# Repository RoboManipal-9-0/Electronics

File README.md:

# Electronics

All the CAD files of the PCBs that electronics team designs goes here

## Note for Users

Only master branch has completed CAD, so make sure to use only them.

## Note for Collaboraters

Before doing anything here learn how to use git version control(different from github), i'll attach the links below
- [Introduction to git- core concepts](https://youtu.be/uR6G2v_WsRA)
- [Introduction to git- Branching and Merging](https://youtu.be/FyAAIHHClqI)
- [Introduction to git- Remotes](https://youtu.be/Gg4bLk8cGNo)

Create a branch with the name of your board that you are working on and start working on that. If two people are woking on same board, add your name at the end seperated with a "-". Don't push any incomplete work to master, keep it clean.

Once you are done designing everthing, add the gerber files in a seperate zip file, merge your branch to master and delete the branch.

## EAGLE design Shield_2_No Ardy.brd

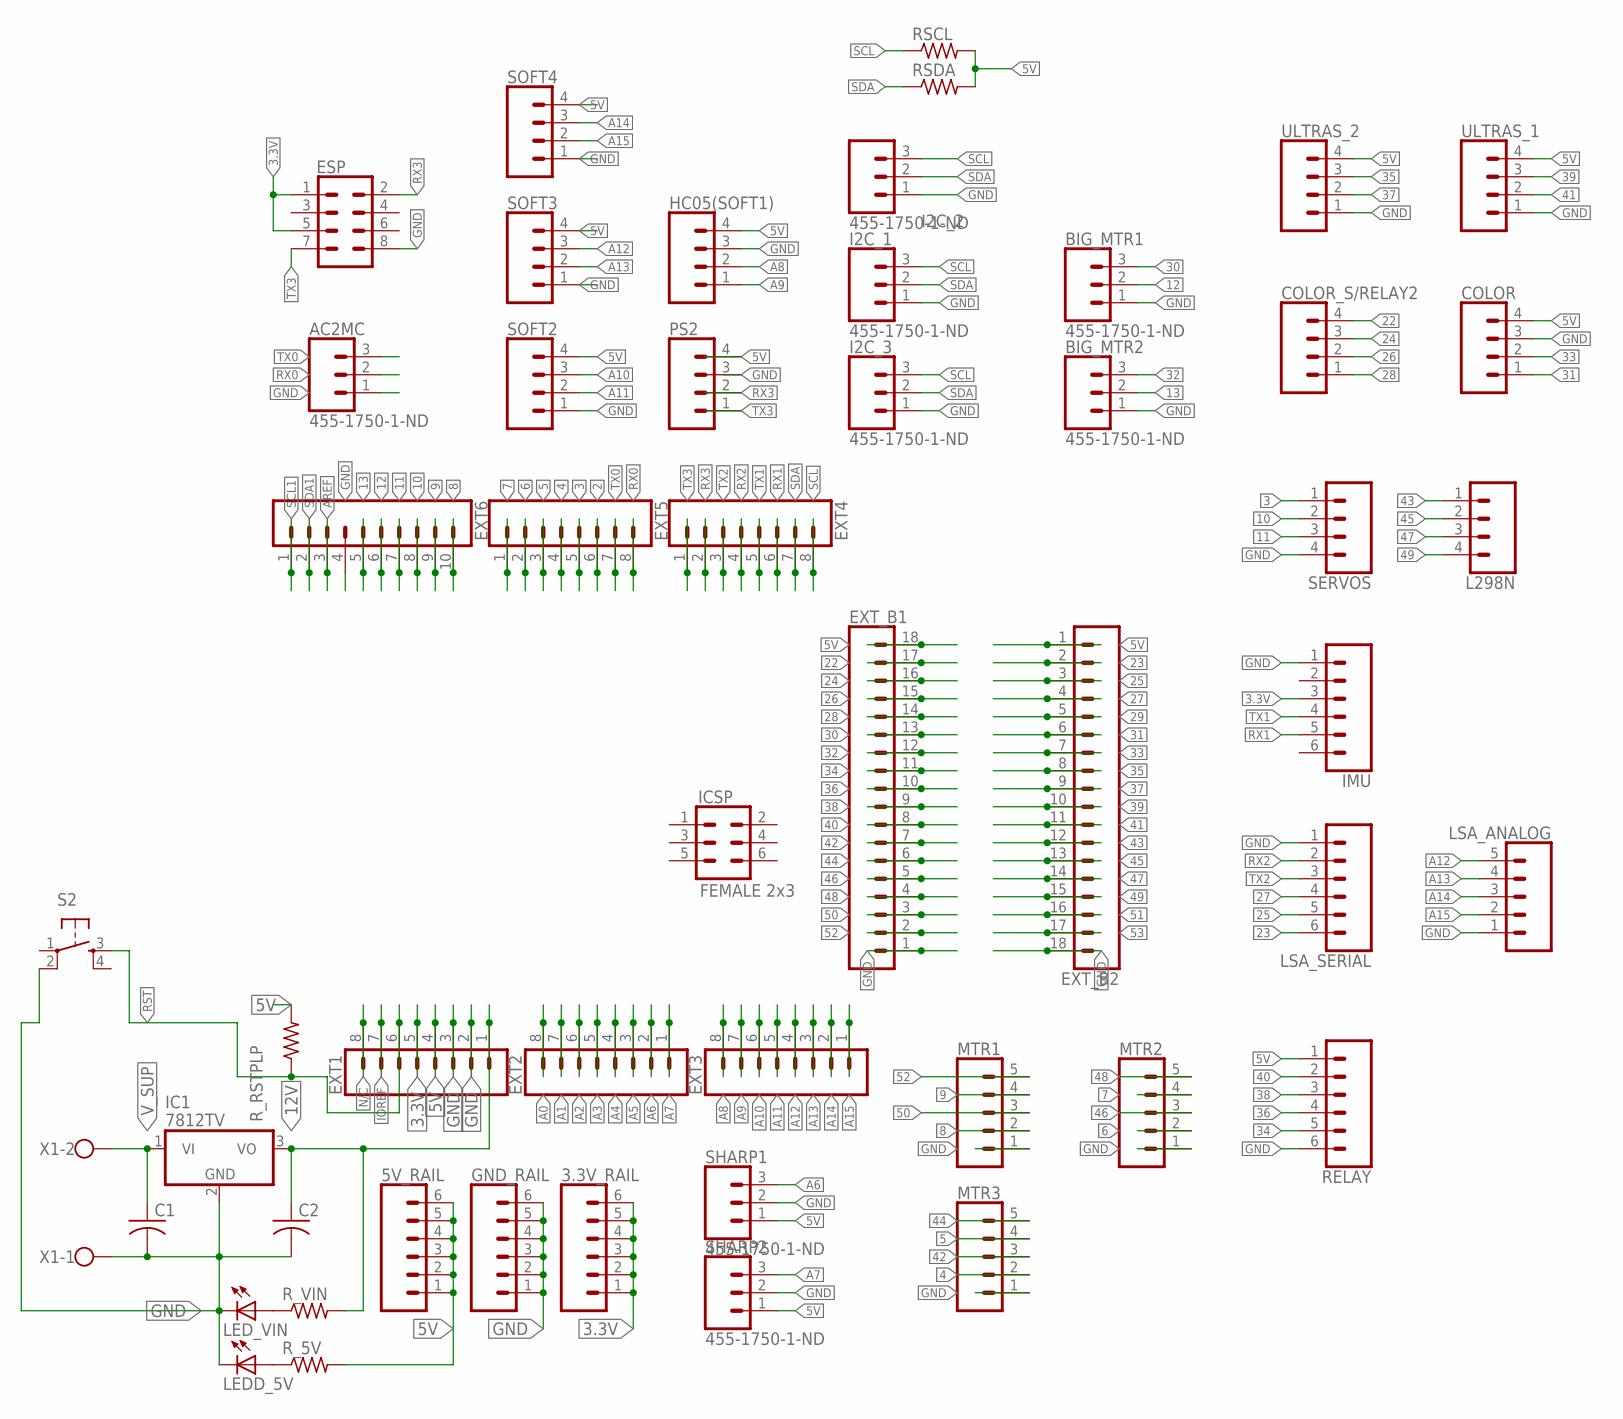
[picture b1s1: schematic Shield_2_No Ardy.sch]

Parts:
3.3V_RAIL, 5V_RAIL: CONN_06SILK_FEMALE_PTH; 1X06
AC2MC: 455-1750-1-ND; 1X03
BIG_MTR1, BIG_MTR2: 455-1750-1-ND; 1X03
C1, C2: C-US025-024X044; C025-024X044
COLOR: CONN_04; 1X04
COLOR_S/RELAY2: CONN_04; 1X04
ESP: CONN_04X2; 2X4
EXT1, EXT2, EXT3, EXT4, EXT5: CONN_08"; 1X08
EXT6: CONN_10"; 1X10
EXT_B1, EXT_B2: CONN_18; 1X18_NO_SILK
GND_RAIL: CONN_06SILK_FEMALE_PTH; 1X06
HC05(SOFT1): CONN_04; 1X04
I2C_1, I2C_2, I2C_3: 455-1750-1-ND; 1X03
IC1: 7812TV; TO220V
ICSP: FEMALE 2x3; 2X3
IMU: CONN_06SILK_FEMALE_PTH; 1X06
L298N: CONN_04; 1X04
LEDD_5V: LED5MM
LED_VIN: LED5MM
LSA_ANALOG: CONN_05; 1X05
LSA_SERIAL: CONN_06SILK_FEMALE_PTH; 1X06
MTR1, MTR2, MTR3: CONN_05; 1X05
PS2: CONN_04; 1X04
RELAY: CONN_06SILK_FEMALE_PTH; 1X06
RSCL: R-US_0204/7; 0204/7
RSDA: R-US_0204/7; 0204/7
R_5V: R-US_0204/7; 0204/7
R_RSTPLP: R-US_0204/7; 0204/7
R_VIN: R-US_0204/7; 0204/7
S2: TAC_SWITCHPTH; TACTILE-PTH
SERVOS: CONN_04; 1X04
SHARP1, SHARP2: 455-1750-1-ND; 1X03
SOFT2, SOFT3, SOFT4: CONN_04; 1X04
ULTRAS_1, ULTRAS_2: CONN_04; 1X04
X1: W237-102

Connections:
2: EXT5.6
3: EXT5.5, SERVOS.1
3.3V: 3.3V_RAIL.1, 3.3V_RAIL.2, 3.3V_RAIL.3, 3.3V_RAIL.4, 3.3V_RAIL.5, 3.3V_RAIL.6, ESP.1, ESP.5, EXT1.5, IMU.3
4: EXT5.4, MTR3.2
5: EXT5.3, MTR3.4
5V: 5V_RAIL.1, 5V_RAIL.2, 5V_RAIL.3, 5V_RAIL.4, 5V_RAIL.5, 5V_RAIL.6, COLOR.4, EXT1.4, EXT_B1.18, EXT_B2.1, HC05(SOFT1).4, PS2.4, RELAY.1, RSCL.2, RSDA.2, R_5V.2, R_RSTPLP.2, SHARP1.1, SHARP2.1, SOFT2.4, SOFT3.4, SOFT4.4, ULTRAS_1.4, ULTRAS_2.4
6: EXT5.2, MTR2.2
7: EXT5.1, MTR2.4
8: EXT6.10, MTR1.2
9: EXT6.9, MTR1.4
10: EXT6.8, SERVOS.2
11: EXT6.7, SERVOS.3
12: BIG_MTR1.2, EXT6.6
12V: C2.1, EXT1.1, IC1.3 (VO), R_VIN.2
13: BIG_MTR2.2, EXT6.5
22: COLOR_S/RELAY2.4, EXT_B1.17
23: EXT_B2.2, LSA_SERIAL.6
24: COLOR_S/RELAY2.3, EXT_B1.16
25: EXT_B2.3, LSA_SERIAL.5
26: COLOR_S/RELAY2.2, EXT_B1.15
27: EXT_B2.4, LSA_SERIAL.4
28: COLOR_S/RELAY2.1, EXT_B1.14
29: EXT_B2.5
30: BIG_MTR1.3, EXT_B1.13
31: COLOR.1, EXT_B2.6
32: BIG_MTR2.3, EXT_B1.12
33: COLOR.2, EXT_B2.7
34: EXT_B1.11, RELAY.5
35: EXT_B2.8, ULTRAS_2.3
36: EXT_B1.10, RELAY.4
37: EXT_B2.9, ULTRAS_2.2
38: EXT_B1.9, RELAY.3
39: EXT_B2.10, ULTRAS_1.3
40: EXT_B1.8, RELAY.2
41: EXT_B2.11, ULTRAS_1.2
42: EXT_B1.7, MTR3.3
43: EXT_B2.12, L298N.1
44: EXT_B1.6, MTR3.5
45: EXT_B2.13, L298N.2
46: EXT_B1.5, MTR2.3
47: EXT_B2.14, L298N.3
48: EXT_B1.4, MTR2.5
49: EXT_B2.15, L298N.4
50: EXT_B1.3, MTR1.3
51: EXT_B2.16
52: EXT_B1.2, MTR1.5
53: EXT_B2.17
A0: EXT2.8
A1: EXT2.7
A2: EXT2.6
A3: EXT2.5
A4: EXT2.4
A5: EXT2.3
A6: EXT2.2, SHARP1.3
A7: EXT2.1, SHARP2.3
A8: EXT3.8, HC05(SOFT1).2
A9: EXT3.7, HC05(SOFT1).1
A10: EXT3.6, SOFT2.3
A11: EXT3.5, SOFT2.2
A12: EXT3.4, LSA_ANALOG.5, SOFT3.3
A13: EXT3.3, LSA_ANALOG.4, SOFT3.2
A14: EXT3.2, LSA_ANALOG.3, SOFT4.3
A15: EXT3.1, LSA_ANALOG.2, SOFT4.2
AREF: EXT6.3
GND: AC2MC.1, BIG_MTR1.1, BIG_MTR2.1, C1.2, C2.2, COLOR.3, ESP.8, EXT1.2, EXT1.3, EXT6.4, EXT_B1.1, EXT_B2.18, GND_RAIL.1, GND_RAIL.2, GND_RAIL.3, GND_RAIL.4, GND_RAIL.5, GND_RAIL.6, HC05(SOFT1).3, I2C_1.1, I2C_2.1, I2C_3.1, IC1.2 (GND), IMU.1, LEDD_5V.K (C), LED_VIN.K (C), LSA_ANALOG.1, LSA_SERIAL.1, MTR1.1, MTR2.1, MTR3.1, PS2.3, RELAY.6, S2.2, SERVOS.4, SHARP1.2, SHARP2.2, SOFT2.1, SOFT3.1, SOFT4.1, ULTRAS_1.1, ULTRAS_2.1, X1.1
IOREF: EXT1.7
unnamed: LED_VIN.A, R_VIN.1
unnamed: LEDD_5V.A, R_5V.1
N/C: EXT1.8
RST: EXT1.6, R_RSTPLP.1, S2.3
RX0: AC2MC.2, EXT5.8
RX1: EXT4.6, IMU.5
RX2: EXT4.4, LSA_SERIAL.2
RX3: ESP.2, EXT4.2, PS2.2
SCL: EXT4.8, I2C_1.3, I2C_2.3, I2C_3.3, RSCL.1
SCL1: EXT6.1
SDA: EXT4.7, I2C_1.2, I2C_2.2, I2C_3.2, RSDA.1
SDA1: EXT6.2
TX0: AC2MC.3, EXT5.7
TX1: EXT4.5, IMU.4
TX2: EXT4.3, LSA_SERIAL.3
TX3: ESP.7, EXT4.1, PS2.1
V_SUP: C1.1, IC1.1 (VI), X1.2

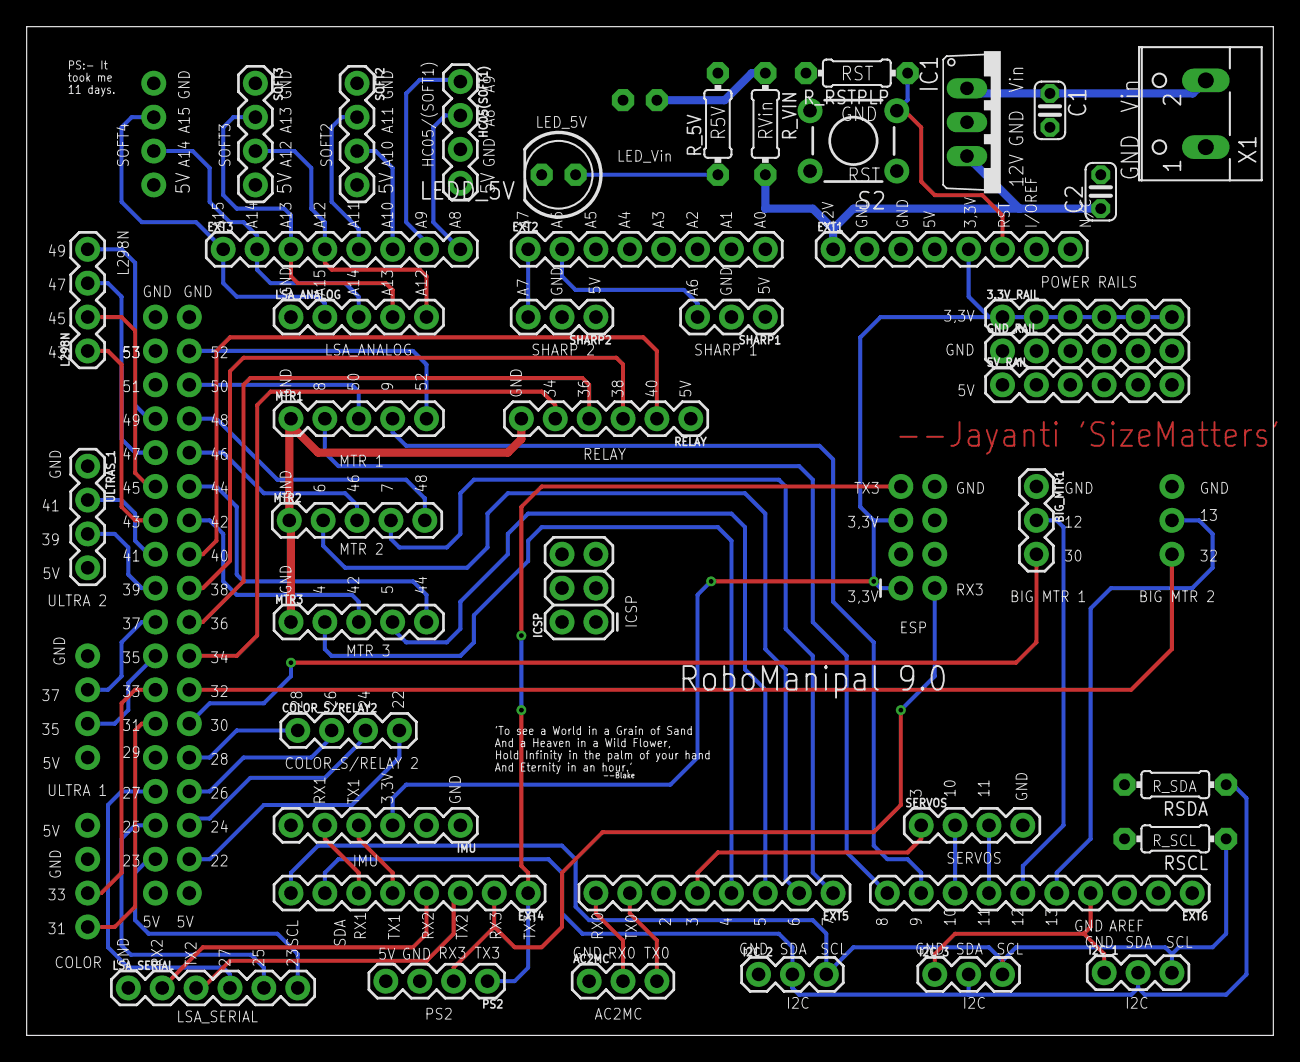
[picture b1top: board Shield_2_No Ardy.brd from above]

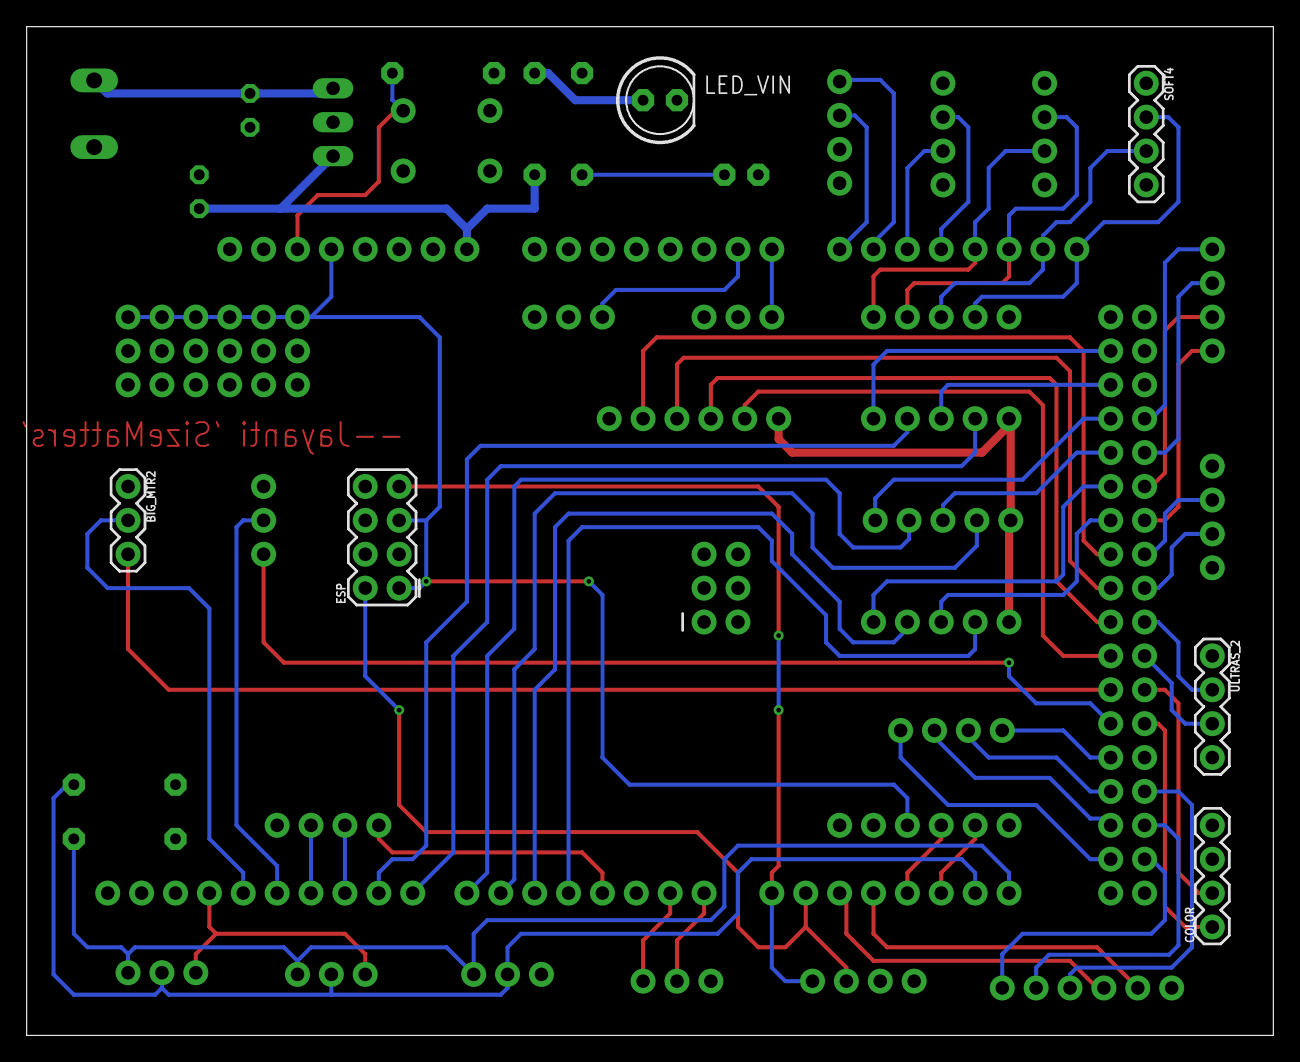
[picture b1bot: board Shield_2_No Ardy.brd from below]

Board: 2 copper layers, 93.5 x 75.6 mm, 51 parts (7 on the bottom side), 68 nets.

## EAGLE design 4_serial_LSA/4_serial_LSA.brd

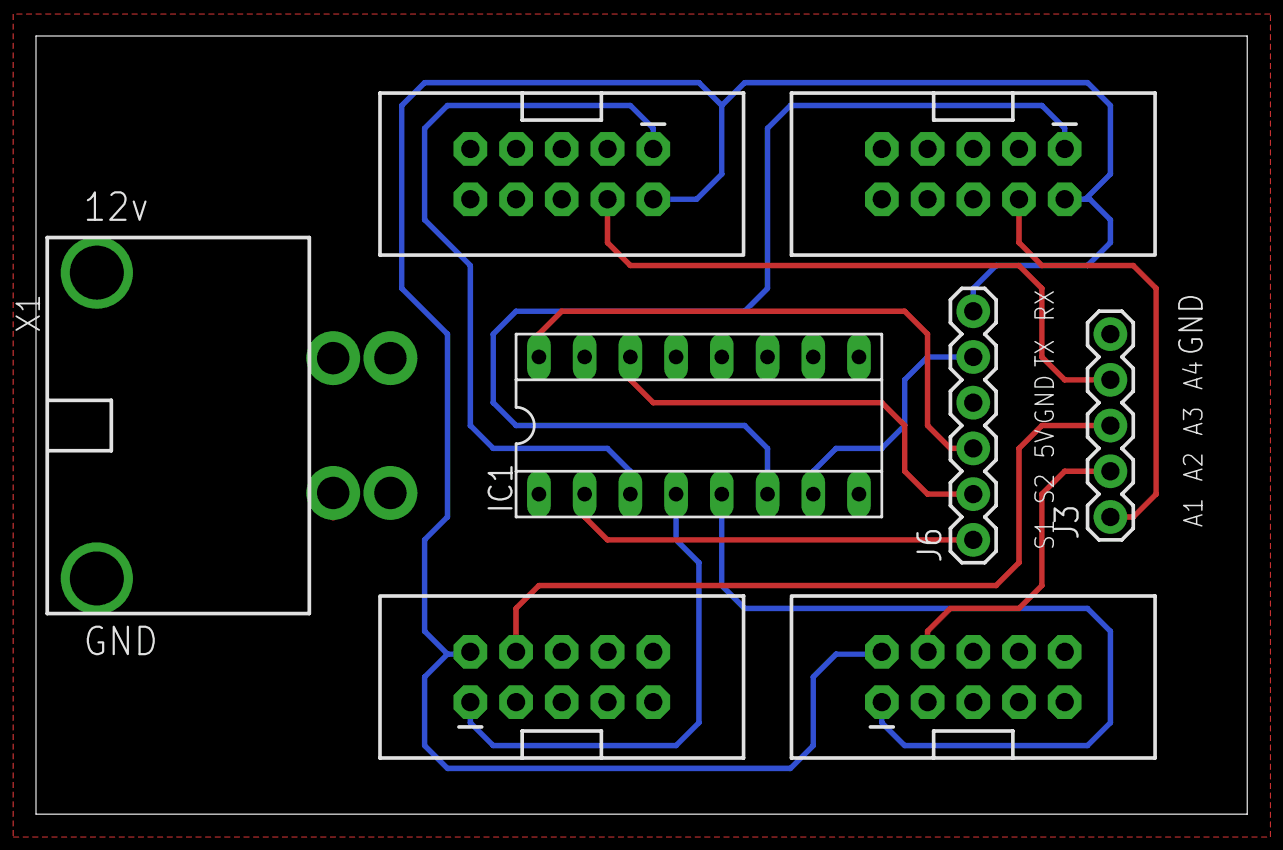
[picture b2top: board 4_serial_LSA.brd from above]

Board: 2 copper layers, 67.3 x 43.2 mm, 8 parts (0 on the bottom side), 15 nets.

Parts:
IC1: SOCKET-16
J3: 1X05
J6: 1X06
LSA1, LSA2, LSA3, LSA4: 2X5-SHROUDED_LOCK
X1: 43160-3102; 43160-XX02

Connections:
5V: IC1.16, J6.3
12V: LSA1.9, LSA2.9, LSA3.9, LSA4.9, X1.1@1
A1: J3.1, LSA1.4
A2: J3.2, LSA2.4
A3: J3.3, LSA3.4
A4: J3.4, LSA4.4
GND: IC1.1, IC1.8, IC1.15, J3.5, J6.4, LSA1.3, LSA1.10, LSA2.3, LSA2.10, LSA3.3, LSA3.10, LSA4.3, LSA4.10, X1.2@1
RX: J6.6, LSA1.2, LSA2.2, LSA3.2, LSA4.2
S0: IC1.14, J6.2
S1: IC1.2, J6.1
TX: IC1.7, J6.5
TX1: IC1.6, LSA1.1
TX2: IC1.5, LSA2.1
TX3: IC1.4, LSA3.1
TX4: IC1.3, LSA4.1

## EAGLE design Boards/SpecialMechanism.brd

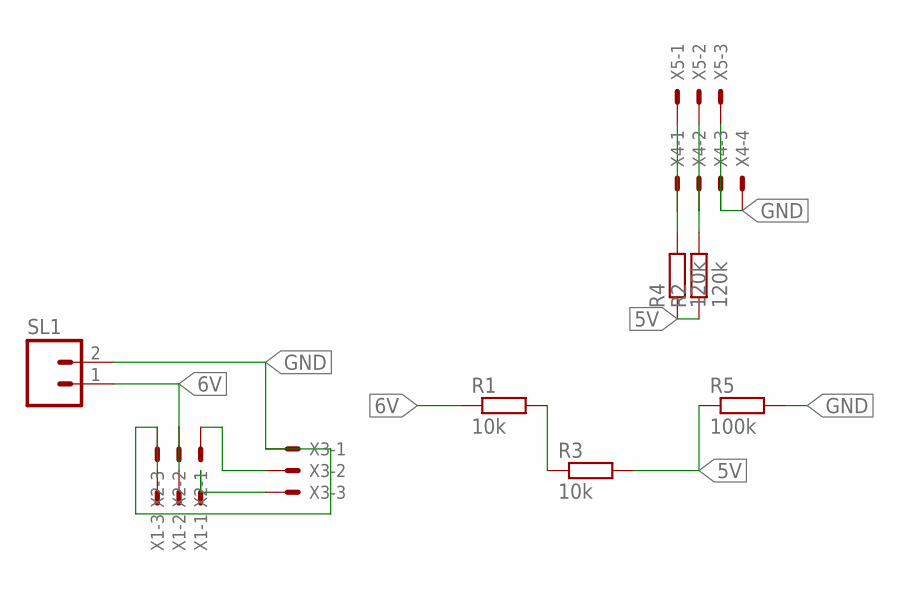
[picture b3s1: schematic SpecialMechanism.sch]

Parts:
R1, R3: 10k; 0207/10
R2, R4: 120k; 0207/10
R5: 100k; 0207/10
SL1: M02; 02P
X1, X2, X3, X5: KK-156-3
X4: KK-156-4

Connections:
5V: R2.1, R3.2, R4.1, R5.1
6V: R1.1, SL1.1, X1.2, X2.2
GND: R5.2, SL1.2, X1.3, X2.3, X3.1, X4.3, X4.4, X5.3
unnamed: R1.2, R3.1
unnamed: X1.1, X3.3
unnamed: X2.1, X3.2
unnamed: R4.2, X4.1, X5.1
unnamed: R2.2, X4.2, X5.2

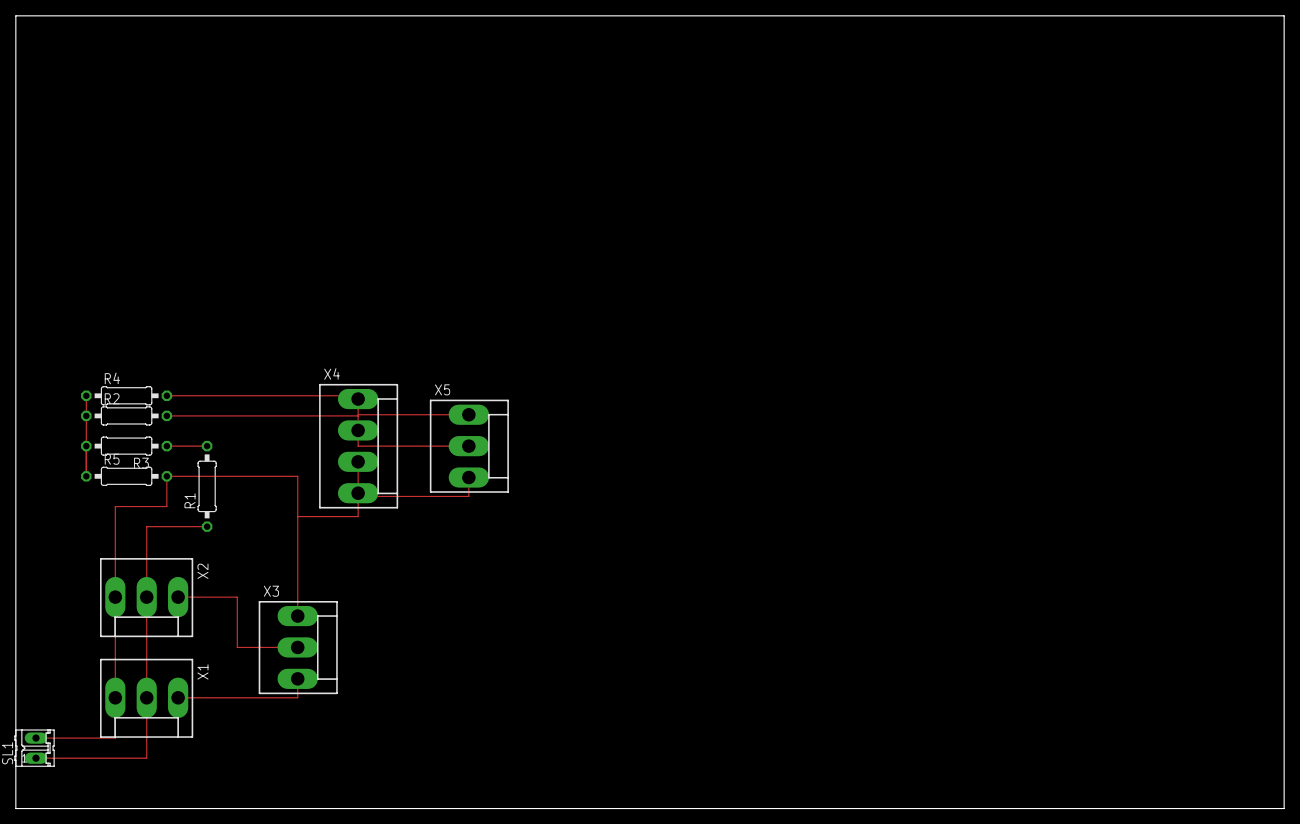
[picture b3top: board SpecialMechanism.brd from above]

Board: 2 copper layers, 160.0 x 100.0 mm, 11 parts (0 on the bottom side), 8 nets.

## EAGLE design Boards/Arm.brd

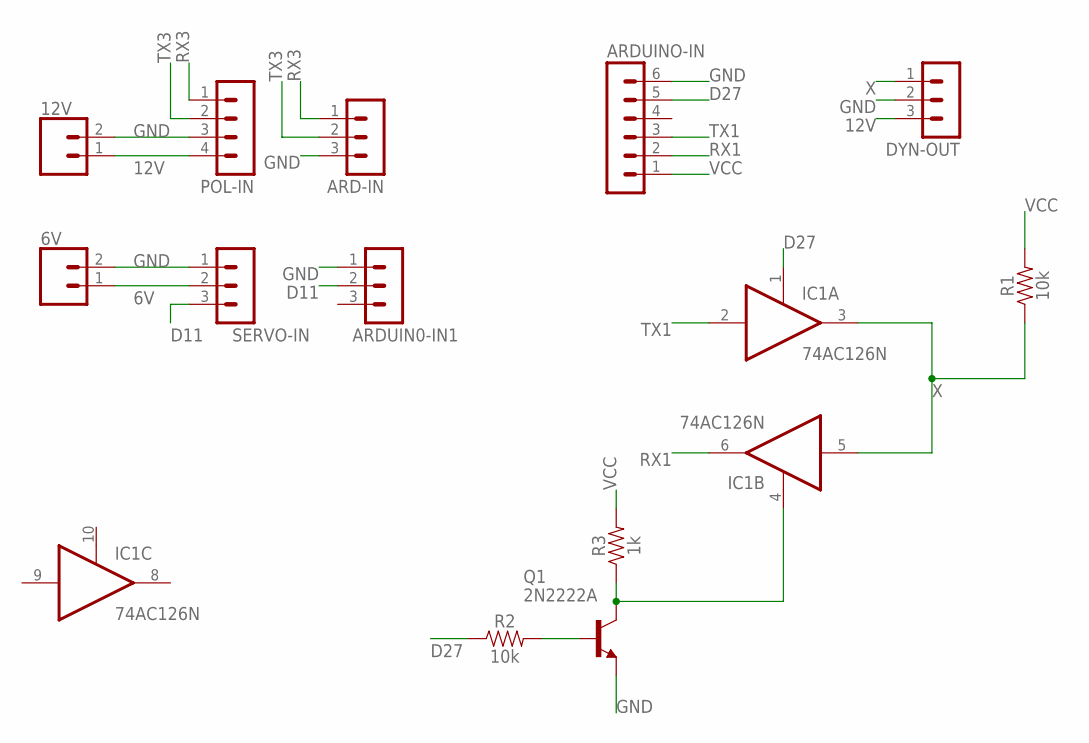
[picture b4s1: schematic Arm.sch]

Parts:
6V, 12V: CONN_021X02_NO_SILK; 1X02_NO_SILK
ARD-IN: MA03-1
ARDUIN0-IN1: MA03-1
ARDUINO-IN: MA06-1
DYN-OUT: MA03-1
IC1: 74AC126N; DIL14
POL-IN: MA04-1
Q1: 2N2222A; TO18
R1, R2: 10k; AXIAL-0.3
R3: 1k; AXIAL-0.3
SERVO-IN: MA03-1

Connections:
6V: 6V.1, SERVO-IN.2
12V: 12V.1, DYN-OUT.3, POL-IN.4
D11: ARDUIN0-IN1.2, SERVO-IN.3
D27: ARDUINO-IN.5, IC1.1 (OE), R2.P$1 (1)
GND: 6V.2, 12V.2, ARD-IN.3, ARDUIN0-IN1.1, ARDUINO-IN.6, DYN-OUT.2, IC1.7 (GND), POL-IN.3, Q1.1 (E), SERVO-IN.1
unnamed: IC1.4 (OE), Q1.3 (C), R3.P$1 (1)
unnamed: Q1.2 (B), R2.P$2 (2)
RX1: ARDUINO-IN.2, IC1.6 (O)
RX3: ARD-IN.1, POL-IN.1
TX1: ARDUINO-IN.3, IC1.2 (I)
TX3: ARD-IN.2, POL-IN.2
VCC: ARDUINO-IN.1, IC1.14 (VCC), R1.P$2 (2), R3.P$2 (2)
X: DYN-OUT.1, IC1.3 (O), IC1.5 (I), R1.P$1 (1)

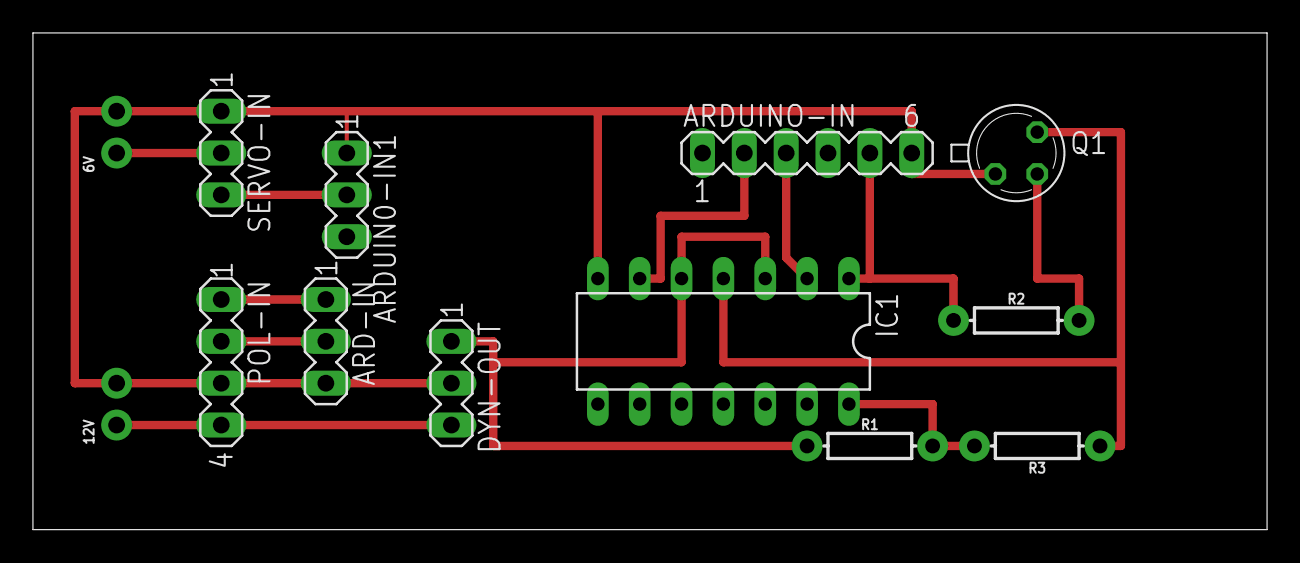
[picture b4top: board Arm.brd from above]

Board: 2 copper layers, 74.9 x 30.1 mm, 13 parts (0 on the bottom side), 13 nets.

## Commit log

2018-09-23 Board Files
2018-09-23 Change name
2018-09-24 WRO BOARDS
2018-10-07 Deleted unusable CADs
2018-10-07 Added RoboCon 2018 Autonomous CAD files
2018-10-07 started power distribution module
2018-10-16 Sparkfun Libraries
2018-10-16 Eagle Libraries
2018-10-16 remove
2018-10-16 Library Changes
2018-10-16 added gitignore files
2018-10-16 added 4 serial LSA shield
2018-10-16 modified .gitignore file
2018-10-17 add the new molex connetor
2018-10-17 minor changes, can be ignored
2018-10-17 4 Serial LSA
2018-10-17 Added gerber files
2018-10-17 Made a fuckup and got the Power distribution back
2018-10-17 Modified Power_distibution schematic
2018-12-10 Added instuctions in the README file.
2018-12-10 Made small changes to README file.
2019-07-29 Added MPU library
2019-07-29 Test commit 1
2019-07-29 Test Commit 2
2020-11-09 removed README.md

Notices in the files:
parts and their libraries:
SparkFun-Connectors: Licensing: Creative Commons ShareAlike 4.0 International - https://creativecommons.org/licenses/by-sa/4.0
